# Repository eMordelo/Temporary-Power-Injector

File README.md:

# Temporary Power Injector

This board uses ModuCard System! If you want to make yourself something more intresting, don't hesitate and check [ModuCard System page](https://github.com/KoNarRobotics/ModuCard-base-module).

## Used tools:

## Features:

INPUT: 12V viá XT60PW horizontal.

OUTPUT: 5V@5A and 12V from input.

Board uses xl4015 to convert 12V to 5V. PCB was not equipped with any safty measures that prevent overcurrent or higher voltage on input.

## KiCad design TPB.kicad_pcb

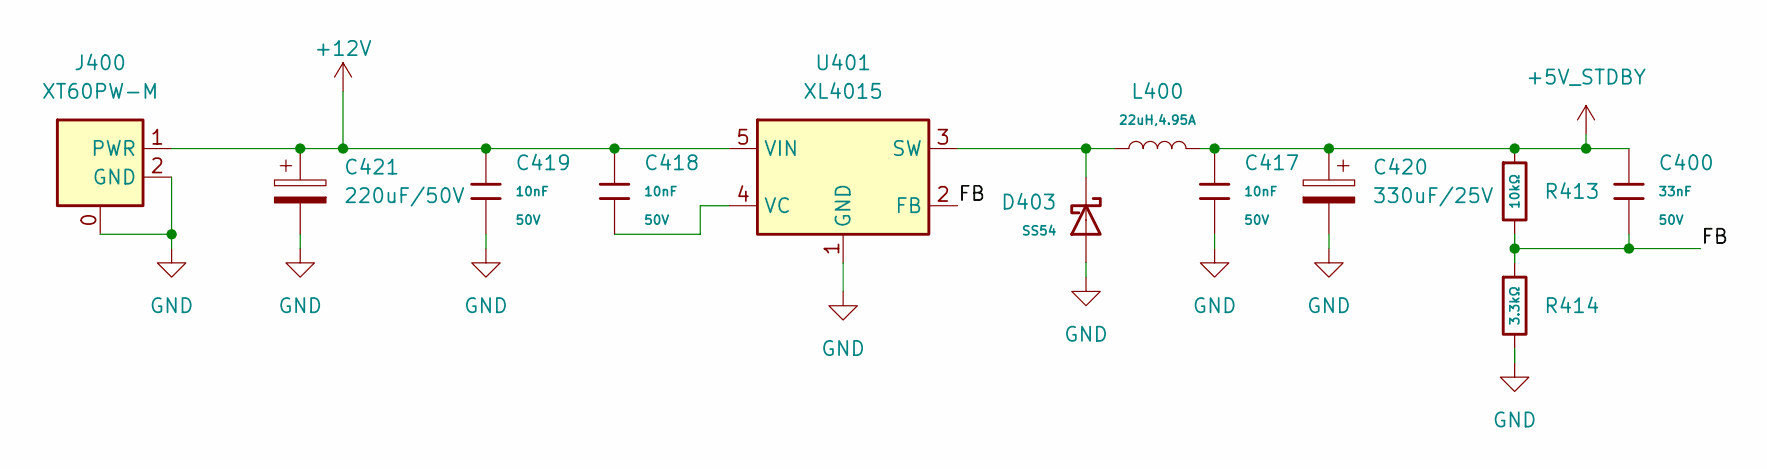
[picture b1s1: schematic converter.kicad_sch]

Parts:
C400: 33nF; C_0603; Voltage Rated 50V; Tolerance ±10%; Part CL10B333KB8NNNC; LCSC C21117
C417, C418, C419: 10nF; C_0603; Voltage Rated 50V; Tolerance ±10%; Part 0603B103K500NT; LCSC C57112
C420: 330uF/25V; CP_Elec_8x10.5
C421: 220uF/50V; CP_Elec_10x10.5
D403: SS54; D_SMA; Forward Voltage (Vf@If) 550mV@5A; Reverse Voltage (Vr) 40V; Part SS54; LCSC C22452
J400: XT60PW-M; XT60PWM; Manufacturer_Part_Number XT60PW-M
L400: 22uH,4.95A; L_SMD,12.5x12.5mm; Part SMDRI129-220MT; LCSC C2924827
R413: 10kΩ; R_0603; Overload Voltage (Max) 75V; Tolerance ±1%; Part 0603WAF1002T5E; LCSC C25804
R414: 3.3kΩ; R_0603; Overload Voltage (Max) 75V; Tolerance ±1%; Part 0603WAF3301T5E; LCSC C22978
U401: XL4015; TO-263-5_TabPin3

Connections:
+5V_STDBY: C400.1, C417.1, C420.1, L400.2, R413.1; also elsewhere on the board
+12V: C418.1, C419.1, C421.1, J400.1 (PWR), U401.5 (VIN); also elsewhere on the board
/converter/FB: C400.2, R413.2, R414.1, U401.2 (FB)
GND: C417.2, C419.2, C420.2, C421.2, D403.2, J400.0, J400.2 (GND), R414.2, U401.1 (GND); also elsewhere on the board
unnamed: D403.1, L400.1, U401.3 (SW)
unnamed: C418.2, U401.4 (VC)

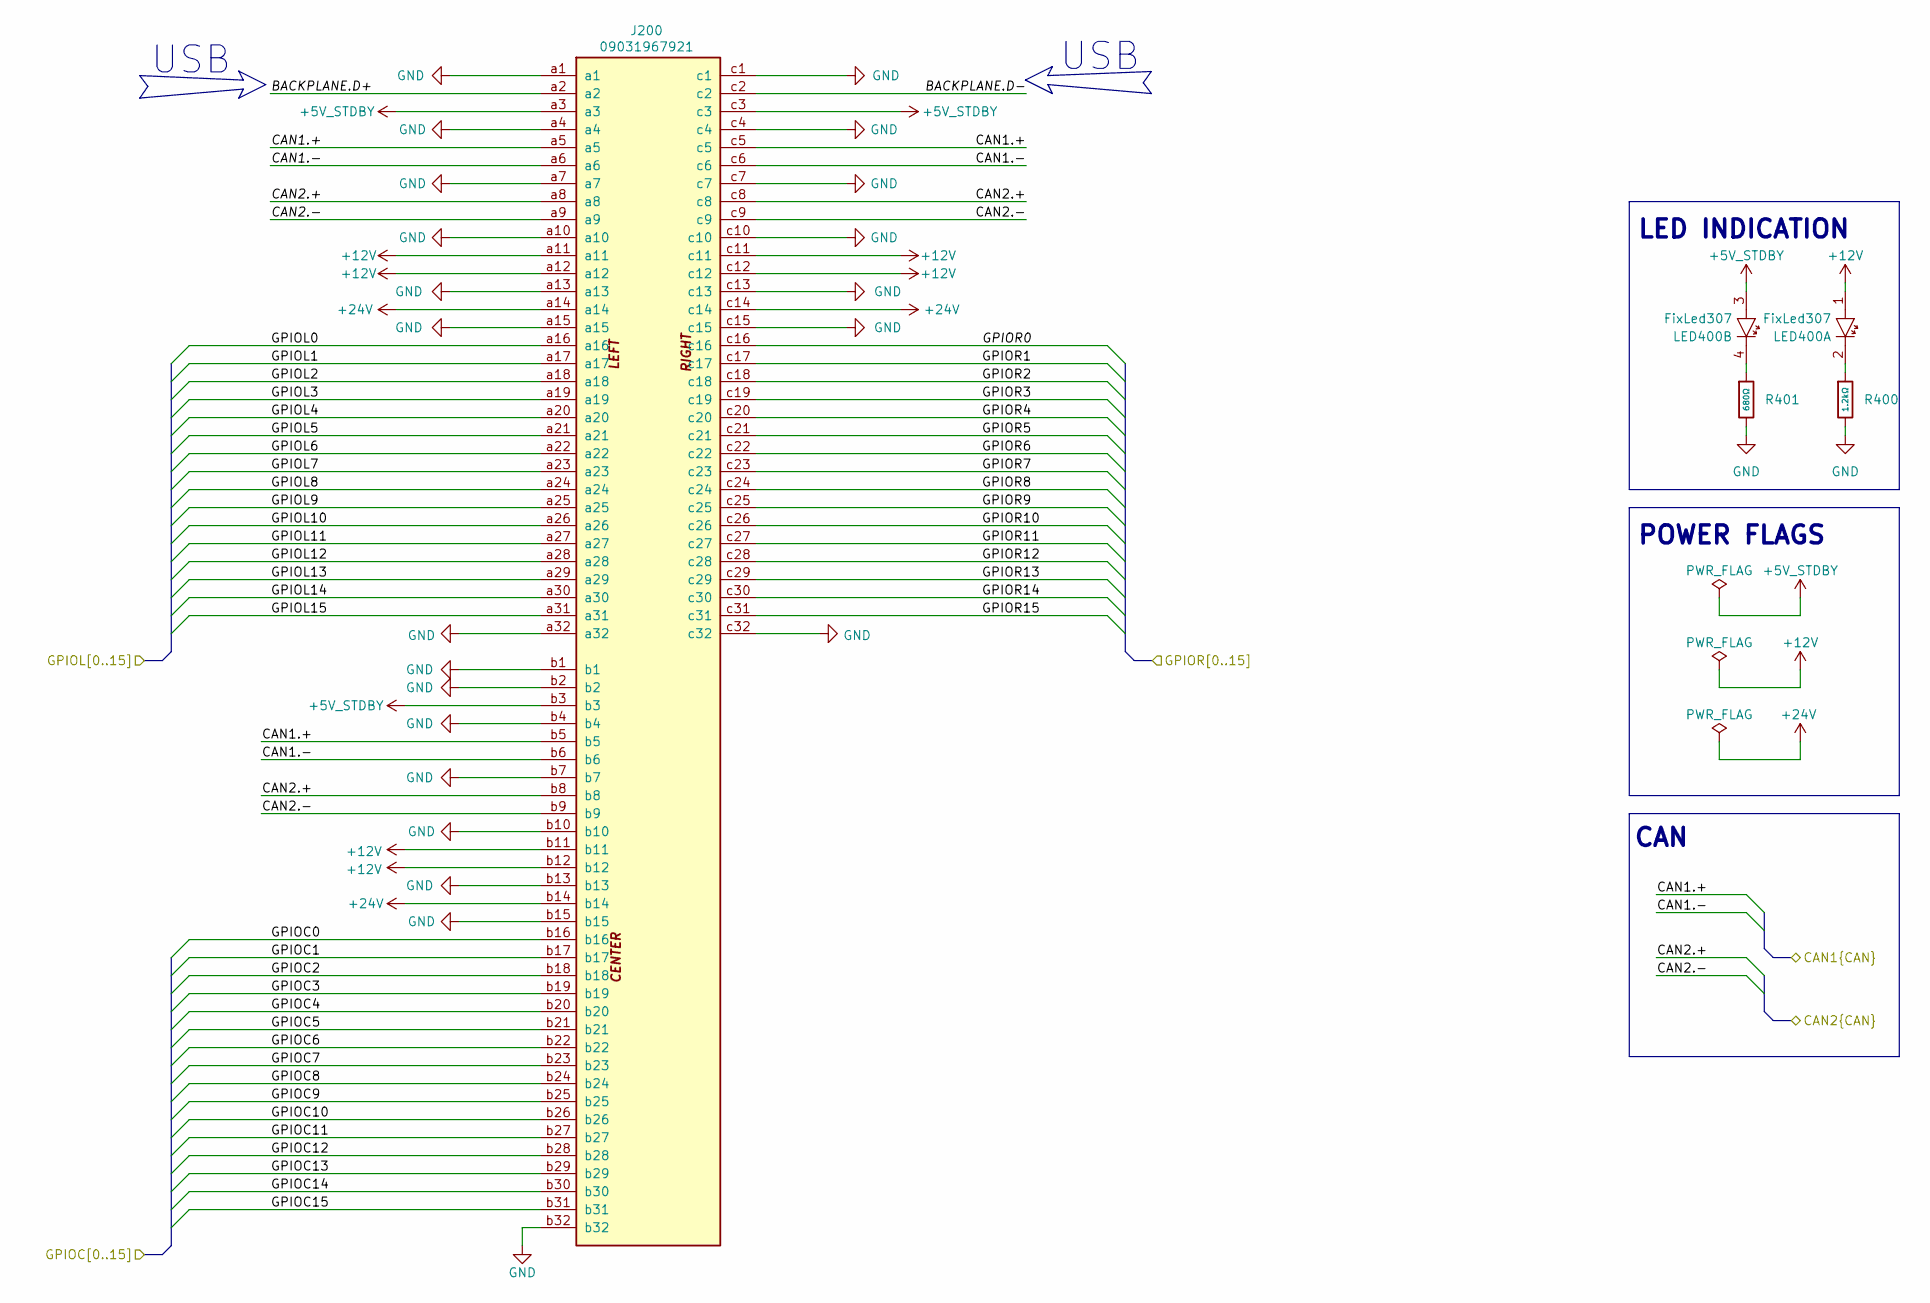
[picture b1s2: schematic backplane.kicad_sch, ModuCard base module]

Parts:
J200: 09031967921; DIN41612_R_3x32_Female_Horizontal_THT; PARTREV D
LED400: FixLed307
R400: 1.2kΩ; R_0805; Overload Voltage (Max) 150V; Tolerance ±1%; Part 0805W8F1201T5E; LCSC C17379
R401: 680Ω; R_0805; Overload Voltage (Max) 150V; Tolerance ±1%; Part 0805W8F6800T5E; LCSC C17798

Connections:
+5V_STDBY: J200.a3, J200.b3, J200.c3, LED400.3; also elsewhere on the board
+12V: J200.a11, J200.a12, J200.b11, J200.b12, J200.c11, J200.c12, LED400.1; also elsewhere on the board
+24V: J200.a14, J200.b14, J200.c14
/Backplane/BACKPLANE.D+: J200.a2
/Backplane/BACKPLANE.D-: J200.c2
/Backplane/CAN1.+: J200.a5, J200.b5, J200.c5
/Backplane/CAN1.-: J200.a6, J200.b6, J200.c6
/Backplane/CAN2.+: J200.a8, J200.b8, J200.c8
/Backplane/CAN2.-: J200.a9, J200.b9, J200.c9
/Backplane/GPIOC0: J200.b16
/Backplane/GPIOC1: J200.b17
/Backplane/GPIOC2: J200.b18
/Backplane/GPIOC3: J200.b19
/Backplane/GPIOC4: J200.b20
/Backplane/GPIOC5: J200.b21
/Backplane/GPIOC6: J200.b22
/Backplane/GPIOC7: J200.b23
/Backplane/GPIOC8: J200.b24
/Backplane/GPIOC9: J200.b25
/Backplane/GPIOC10: J200.b26
/Backplane/GPIOC11: J200.b27
/Backplane/GPIOC12: J200.b28
/Backplane/GPIOC13: J200.b29
/Backplane/GPIOC14: J200.b30
/Backplane/GPIOC15: J200.b31
/Backplane/GPIOL0: J200.a16
/Backplane/GPIOL1: J200.a17
/Backplane/GPIOL2: J200.a18
/Backplane/GPIOL3: J200.a19
/Backplane/GPIOL4: J200.a20
/Backplane/GPIOL5: J200.a21
/Backplane/GPIOL6: J200.a22
/Backplane/GPIOL7: J200.a23
/Backplane/GPIOL8: J200.a24
/Backplane/GPIOL9: J200.a25
/Backplane/GPIOL10: J200.a26
/Backplane/GPIOL11: J200.a27
/Backplane/GPIOL12: J200.a28
/Backplane/GPIOL13: J200.a29
/Backplane/GPIOL14: J200.a30
/Backplane/GPIOL15: J200.a31
/Backplane/GPIOR0: J200.c16
/Backplane/GPIOR1: J200.c17
/Backplane/GPIOR2: J200.c18
/Backplane/GPIOR3: J200.c19
/Backplane/GPIOR4: J200.c20
/Backplane/GPIOR5: J200.c21
/Backplane/GPIOR6: J200.c22
/Backplane/GPIOR7: J200.c23
/Backplane/GPIOR8: J200.c24
/Backplane/GPIOR9: J200.c25
/Backplane/GPIOR10: J200.c26
/Backplane/GPIOR11: J200.c27
/Backplane/GPIOR12: J200.c28
/Backplane/GPIOR13: J200.c29
/Backplane/GPIOR14: J200.c30
/Backplane/GPIOR15: J200.c31
GND: J200.a1, J200.a4, J200.a7, J200.a10, J200.a13, J200.a15, J200.a32, J200.b1, J200.b2, J200.b4, J200.b7, J200.b10, J200.b13, J200.b15, J200.b32, J200.c1, J200.c4, J200.c7, J200.c10, J200.c13, J200.c15, J200.c32, R400.2, R401.2; also elsewhere on the board
unnamed: LED400.2, R400.1
unnamed: LED400.4, R401.1

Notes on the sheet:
USB
LED INDICATION
CAN
POWER FLAGS

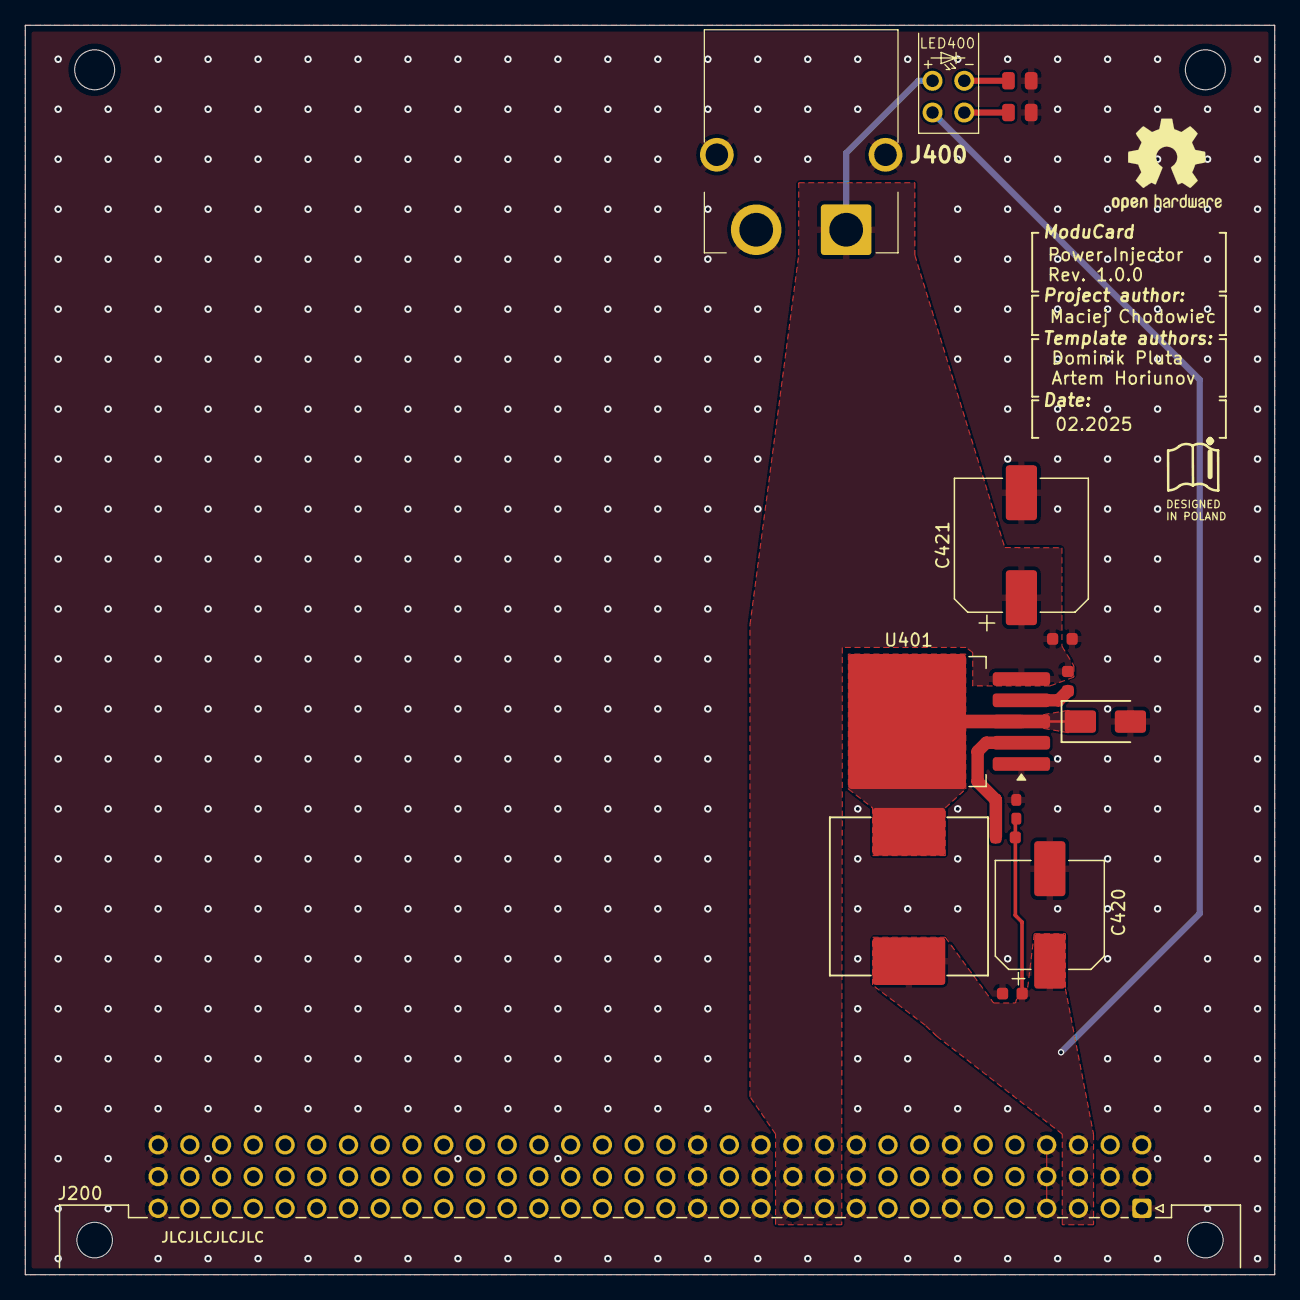
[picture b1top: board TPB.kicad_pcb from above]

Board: 2 copper layers, 100.0 x 100.0 mm, 16 parts (0 on the bottom side), 13 nets.

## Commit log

2025-02-19 copy of moducard
2025-02-19 Converter schematic added
2025-02-19 PCB layout added
2025-02-20 Improve to traces
2025-02-20 Add XT60PW-F and Implement
2025-02-20 change LED Indicator
    also most wide tracks changed to polygons
2025-02-20 RDC warnings removed
    All warnings and crucial errors has been removed.
2025-02-20 Add generated schematic PDF and Gerber files
2025-02-20 Update README.md
    Main title has been changed to project name.
2025-02-21 add LED list on back
2025-02-21 add DRC exclusons
2025-02-21 add Gerger
    add Gerger, add jlc number
